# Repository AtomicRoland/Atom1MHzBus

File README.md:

This KiCAD project is an 1 MHz bus interface for the Acorn Atom and Acorn System series computers. It provides both 1 MHz bus and BBC Micro compatible User Port. The 6522 
of the Atom or System CPU board is used for the User Port interface. The AB connector is placed on the board in a way that you can easily swap both rows. It might be necessary 
to shorten the board to the printed line at the solder side, next to the AB connector.

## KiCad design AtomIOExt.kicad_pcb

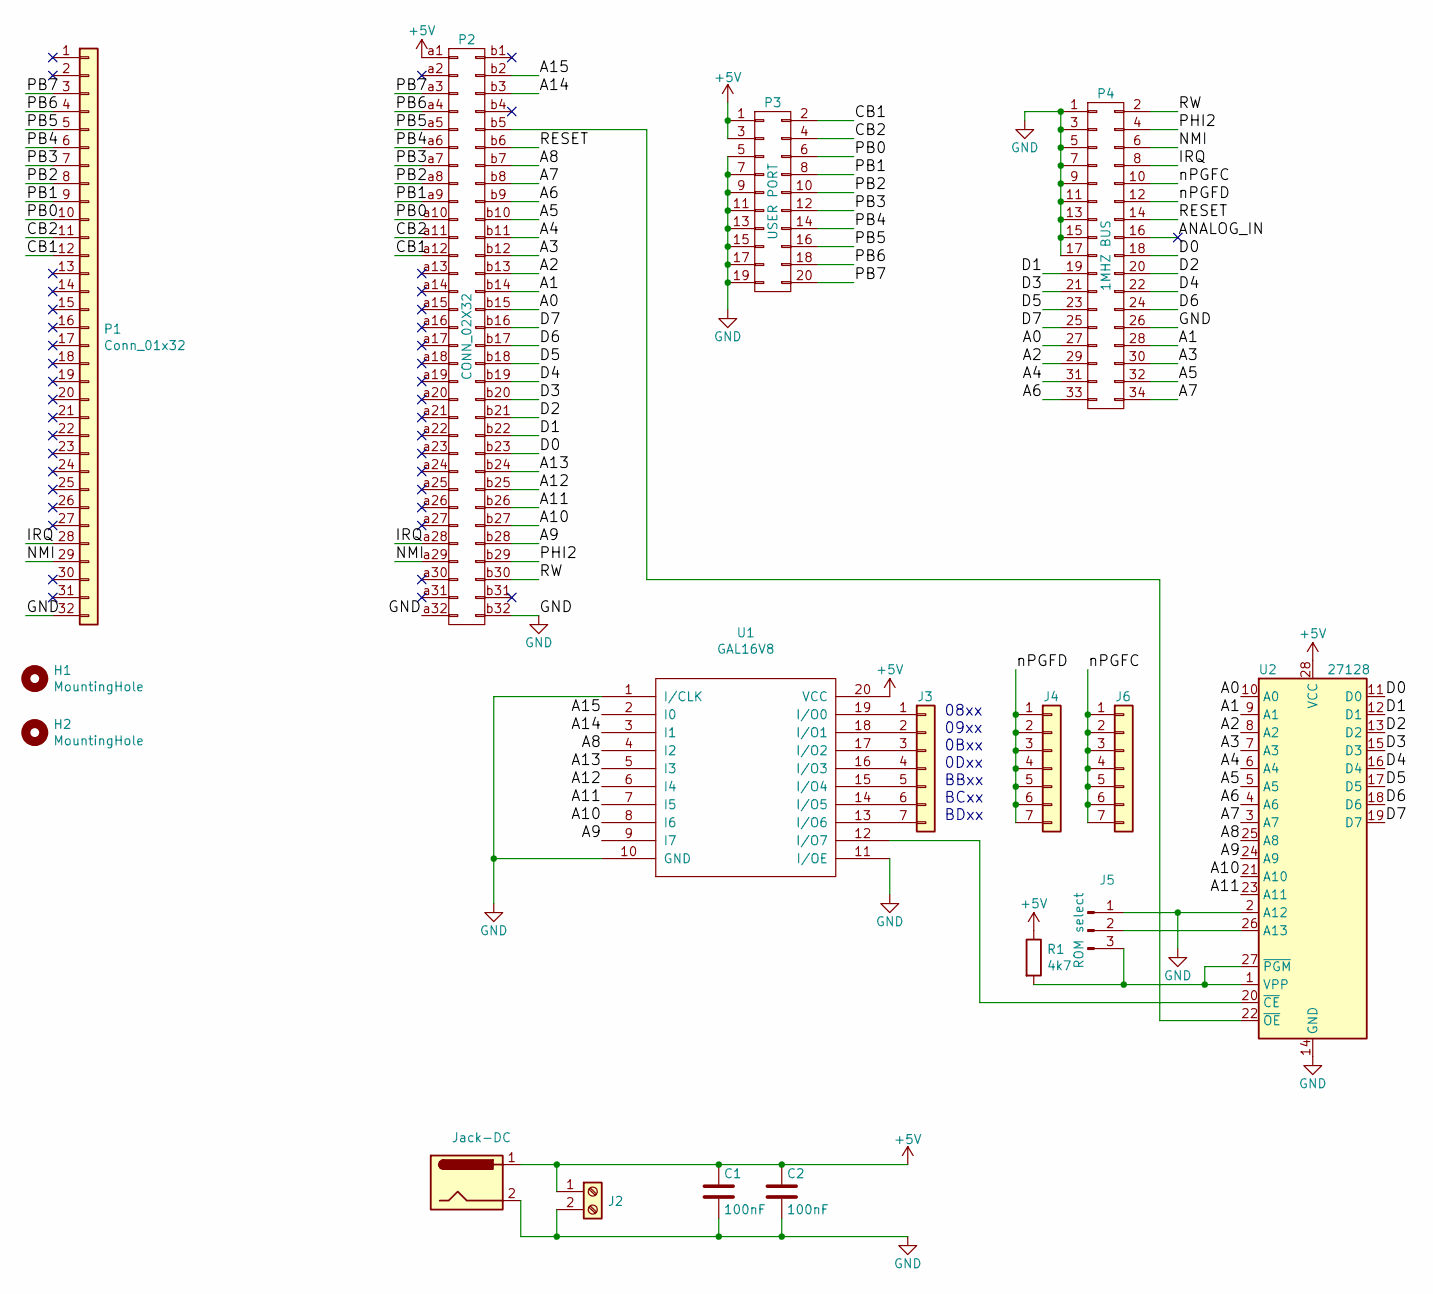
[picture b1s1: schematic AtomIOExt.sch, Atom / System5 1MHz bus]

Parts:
C1, C2: 100nF; C_Disc_D5.0mm_W2.5mm_P5.00mm
H1, H2: MountingHole; MountingHole_4.3mm_M4
J1: Jack-DC; BarrelJack_Horizontal
J2: Screw_Terminal_01x02; TerminalBlock_MetzConnect_Type101_RT01602HBWC_1x02_P5.08mm_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
J3, J4, J6: Conn_01x07; PinHeader_1x07_P2.54mm_Vertical
J5: ROM select; PinHeader_1x03_P2.54mm_Vertical
P1: Conn_01x32; PinHeader_1x32_P2.54mm_Vertical
P2: CONN_02X32; DIN41612_B_2x32_Horizontal
P3: USER PORT; IDC-Header_2x10_P2.54mm_Vertical
P4: 1MHZ BUS; IDC-Header_2x17_P2.54mm_Vertical
R1: 4k7; R_Axial_DIN0411_L9.9mm_D3.6mm_P12.70mm_Horizontal
U1: GAL16V8; DIP-20_W7.62mm_LongPads
U2: 27128; DIP-28_W15.24mm

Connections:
+5V: C1.1, C2.1, J1.1, J2.1, P2.a1, P3.1, P3.3, R1.1, U1.20 (VCC), U2.28 (VCC)
/A0: P2.b15, P4.27, U2.10 (A0)
/A1: P2.b14, P4.28, U2.9 (A1)
/A2: P2.b13, P4.29, U2.8 (A2)
/A3: P2.b12, P4.30, U2.7 (A3)
/A4: P2.b11, P4.31, U2.6 (A4)
/A5: P2.b10, P4.32, U2.5 (A5)
/A6: P2.b9, P4.33, U2.4 (A6)
/A7: P2.b8, P4.34, U2.3 (A7)
/A8: P2.b7, U1.4 (I2), U2.25 (A8)
/A9: P2.b28, U1.9 (I7), U2.24 (A9)
/A10: P2.b27, U1.8 (I6), U2.21 (A10)
/A11: P2.b26, U1.7 (I5), U2.23 (A11)
/A12: P2.b25, U1.6 (I4)
/A13: P2.b24, U1.5 (I3)
/A14: P2.b3, U1.3 (I1)
/A15: P2.b2, U1.2 (I0)
/CB1: P1.12, P2.a12, P3.2
/CB2: P1.11, P2.a11, P3.4
/D0: P2.b23, P4.18, U2.11 (D0)
/D1: P2.b22, P4.19, U2.12 (D1)
/D2: P2.b21, P4.20, U2.13 (D2)
/D3: P2.b20, P4.21, U2.15 (D3)
/D4: P2.b19, P4.22, U2.16 (D4)
/D5: P2.b18, P4.23, U2.17 (D5)
/D6: P2.b17, P4.24, U2.18 (D6)
/D7: P2.b16, P4.25, U2.19 (D7)
/IRQ: P1.28, P2.a28, P4.8
/NMI: P1.29, P2.a29, P4.6
/PB0: P1.10, P2.a10, P3.6
/PB1: P1.9, P2.a9, P3.8
/PB2: P1.8, P2.a8, P3.10
/PB3: P1.7, P2.a7, P3.12
/PB4: P1.6, P2.a6, P3.14
/PB5: P1.5, P2.a5, P3.16
/PB6: P1.4, P2.a4, P3.18
/PB7: P1.3, P2.a3, P3.20
/PHI2: P2.b29, P4.4
/RESET: P2.b6, P4.14
/RW: P2.b30, P4.2
/nPGFC: J6.1, J6.2, J6.3, J6.4, J6.5, J6.6, J6.7, P4.10
/nPGFD: J4.1, J4.2, J4.3, J4.4, J4.5, J4.6, J4.7, P4.12
GND: C1.2, C2.2, J1.2, J2.2, J5.1, P1.32, P2.a32, P2.b32, P3.5, P3.7, P3.9, P3.11, P3.13, P3.15, P3.17, P3.19, P4.1, P4.3, P4.5, P4.7, P4.9, P4.11, P4.13, P4.15, P4.17, P4.26, U1.1 (I/CLK), U1.10 (GND), U1.11 (I/OE), U2.2 (A12), U2.14 (GND)
unnamed: J3.1, U1.19 (I/O0)
unnamed: J3.2, U1.18 (I/O1)
unnamed: J3.3, U1.17 (I/O2)
unnamed: J3.4, U1.16 (I/O3)
unnamed: J3.5, U1.15 (I/O4)
unnamed: J3.6, U1.14 (I/O5)
unnamed: J3.7, U1.13 (I/O6)
unnamed: J5.2, U2.26 (A13)
unnamed: J5.3, R1.2, U2.1 (VPP), U2.27 (~PGM)
unnamed: P2.b5, U2.22 (~OE)
unnamed: U1.12 (I/O7), U2.20 (~CE)

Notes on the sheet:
08xx 09xx 0Bxx 0Dxx BBxx BCxx BDxx

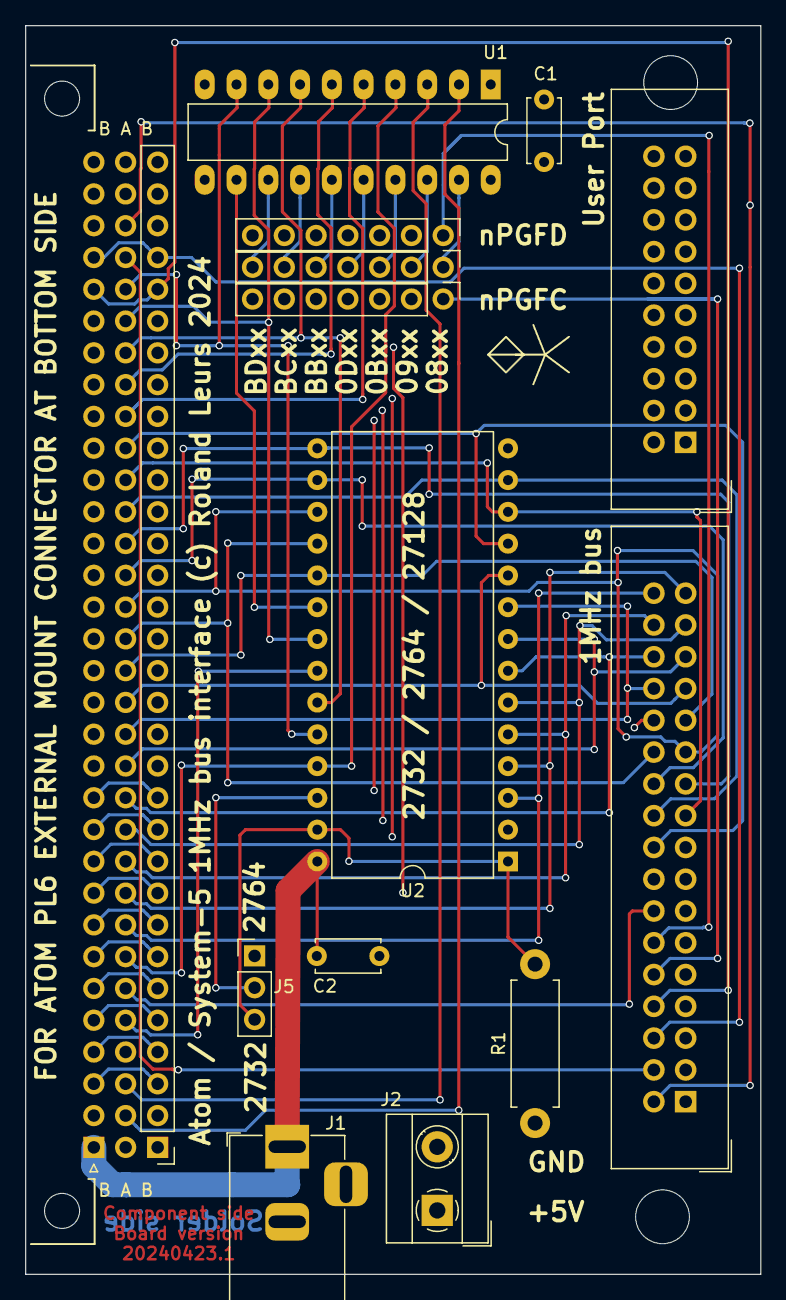
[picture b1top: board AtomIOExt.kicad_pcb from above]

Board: 4 copper layers, 58.8 x 99.8 mm, 17 parts (0 on the bottom side), 54 nets.

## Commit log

2024-08-25 Add files via upload
    Initial commit
